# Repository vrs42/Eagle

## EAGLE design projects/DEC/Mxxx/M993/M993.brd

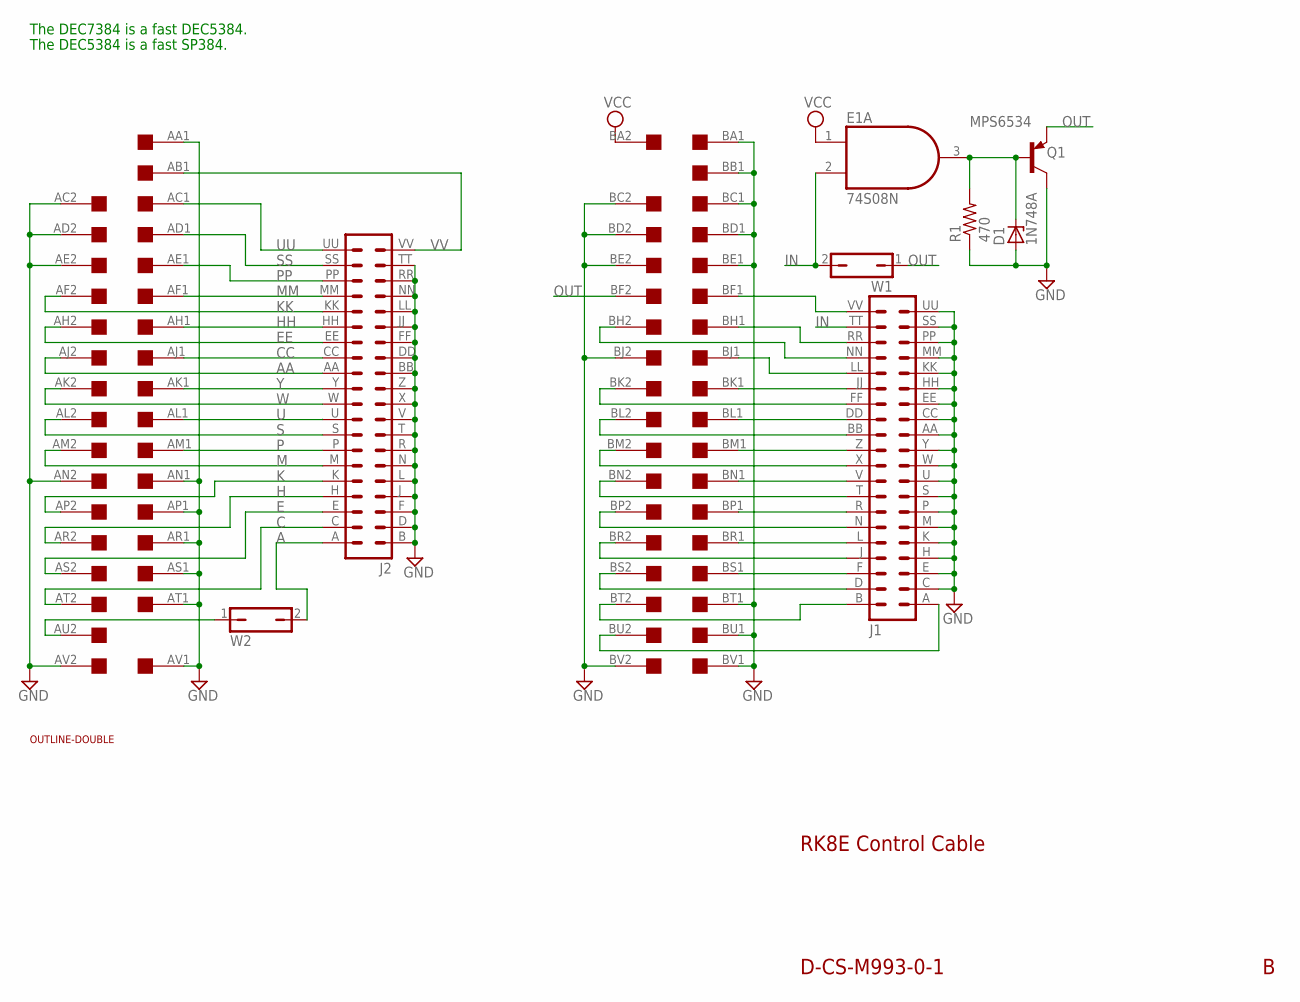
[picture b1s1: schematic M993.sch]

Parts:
D1: 1N748A; ZDIO-10
E1: 74S08N; DIL14
J1, J2: DEC40PINH
Q1: MPS6534; TO92
R1: 470; 0207/10
U$1: OUTLINE-DOUBLE; DOUBLE
U$2: DOUBLE; EDGE-CON4
W1, W2: JP1Q; JP1

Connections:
A: J2.A (1), W2.2
AA: J2.AA (23), U$2.AJ2
C: J2.C (3), U$2.AT2
CC: J2.CC (25), U$2.AJ1
E: J2.E (5), U$2.AS2
EE: J2.EE (27), U$2.AH2
GND: D1.A, E1.7 (GND), J1.AA (23), J1.C (3), J1.CC (25), J1.E (5), J1.EE (27), J1.H (7), J1.HH (29), J1.K (9), J1.KK (31), J1.M (11), J1.MM (33), J1.P (13), J1.PP (35), J1.S (15), J1.SS (37), J1.U (17), J1.UU (39), J1.W (19), J1.Y (21), J2.B (2), J2.BB (24), J2.D (4), J2.DD (26), J2.F (6), J2.FF (28), J2.J (8), J2.JJ (30), J2.L (10), J2.LL (32), J2.N (12), J2.NN (34), J2.R (14), J2.RR (36), J2.T (16), J2.TT (38), J2.V (18), J2.X (20), J2.Z (22), Q1.3 (C), R1.1, U$2.AA1, U$2.AC2, U$2.AD2, U$2.AE2, U$2.AN1, U$2.AN2, U$2.AP1, U$2.AR1, U$2.AS1, U$2.AT1, U$2.AV1, U$2.AV2, U$2.BA1, U$2.BB1, U$2.BC1, U$2.BC2, U$2.BD1, U$2.BD2, U$2.BE1, U$2.BE2, U$2.BJ2, U$2.BT1, U$2.BU1, U$2.BV1, U$2.BV2
H: J2.H (7), U$2.AR2
HH: J2.HH (29), U$2.AH1
IN: E1.2 (I1), J1.TT (38), W1.2
K: J2.K (9), U$2.AP2
KK: J2.KK (31), U$2.AF2
M: J2.M (11), U$2.AM2
MM: J2.MM (33), U$2.AF1
unnamed: U$2.AU2, W2.1
unnamed: D1.C, E1.3 (O), Q1.2 (B), R1.2
unnamed: J1.D (4), U$2.BS2
unnamed: J1.F (6), U$2.BS1
unnamed: J1.J (8), U$2.BR2
unnamed: J1.L (10), U$2.BR1
unnamed: J1.N (12), U$2.BP2
unnamed: J1.R (14), U$2.BP1
unnamed: J1.T (16), U$2.BN2
unnamed: J1.A (1), U$2.BU2
unnamed: J1.B (2), U$2.BT2
unnamed: J1.V (18), U$2.BN1
unnamed: J1.X (20), U$2.BM2
unnamed: J1.Z (22), U$2.BM1
unnamed: J1.BB (24), U$2.BL2
unnamed: J1.DD (26), U$2.BL1
unnamed: J1.FF (28), U$2.BK2
unnamed: J1.JJ (30), U$2.BK1
unnamed: J1.LL (32), U$2.BJ1
unnamed: J1.NN (34), U$2.BH2
unnamed: J1.RR (36), U$2.BH1
unnamed: J1.VV (40), U$2.BF1
OUT: Q1.1 (E), U$2.BF2, W1.1
P: J2.P (13), U$2.AM1
PP: J2.PP (35), U$2.AE1
S: J2.S (15), U$2.AL2
SS: J2.SS (37), U$2.AD1
U: J2.U (17), U$2.AL1
UU: J2.UU (39), U$2.AC1
VCC: E1.1 (I0), E1.14 (VCC), U$2.BA2
VV: J2.VV (40), U$2.AB1
W: J2.W (19), U$2.AK2
Y: J2.Y (21), U$2.AK1

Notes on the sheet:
The DEC7384 is a fast DEC5384.
The DEC5384 is a fast SP384.
RK8E Control Cable
D-CS-M993-0-1

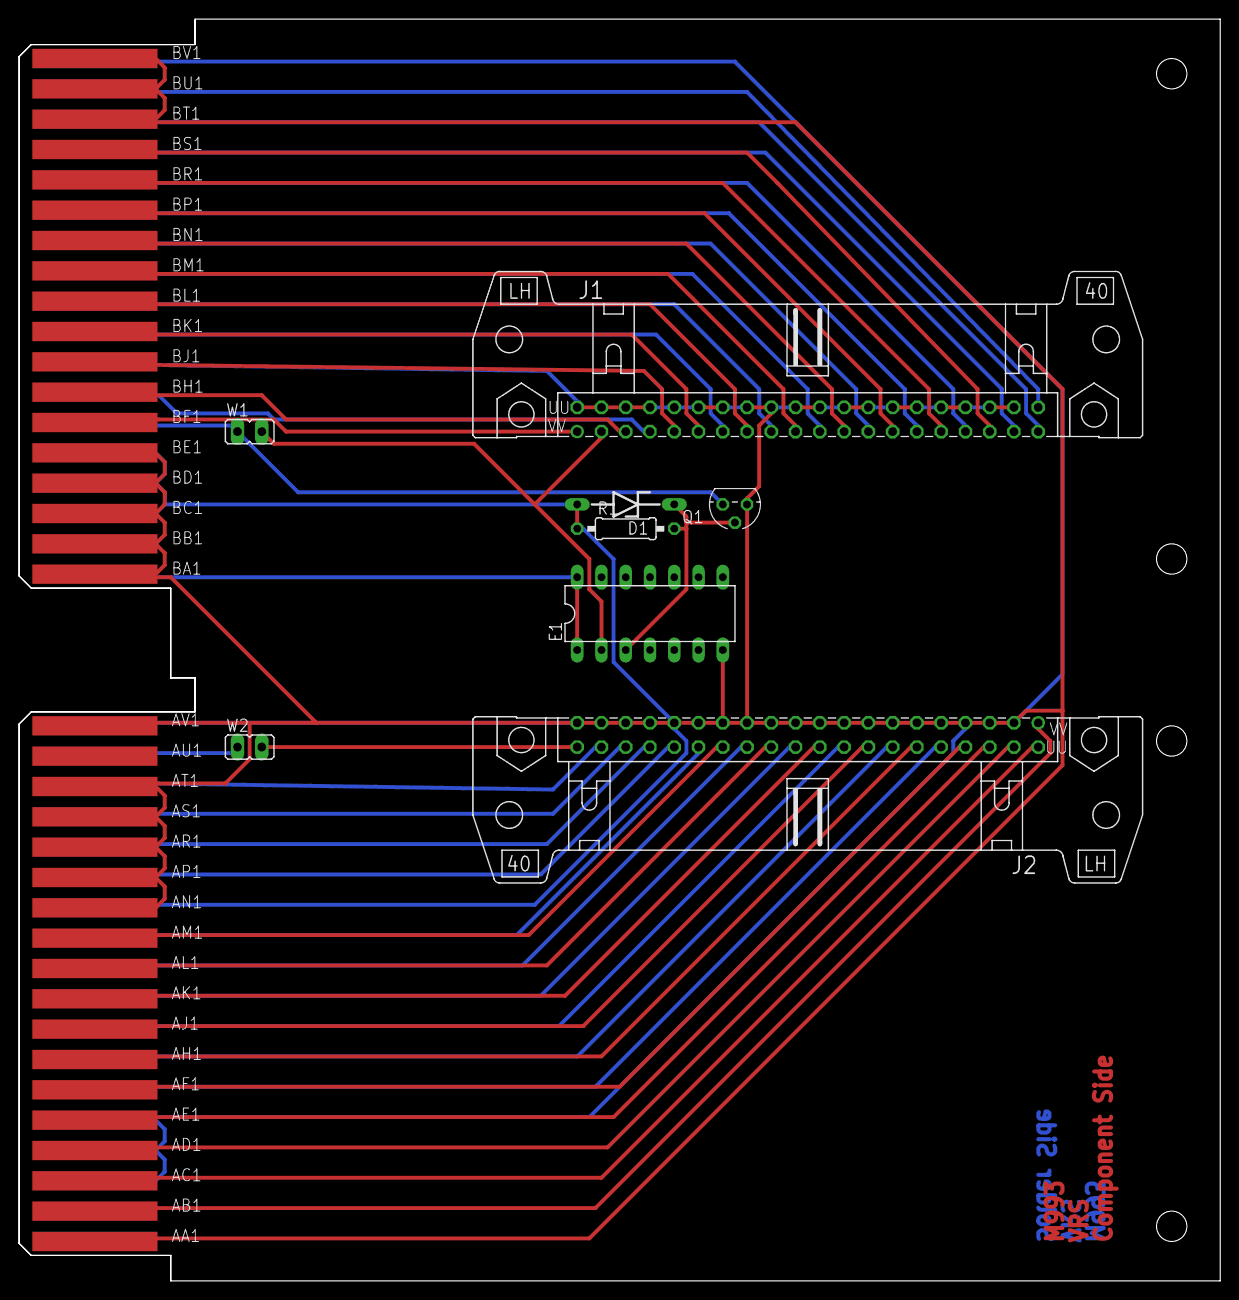
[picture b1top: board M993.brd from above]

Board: 2 copper layers, 125.7 x 132.1 mm, 10 parts (0 on the bottom side), 47 nets.

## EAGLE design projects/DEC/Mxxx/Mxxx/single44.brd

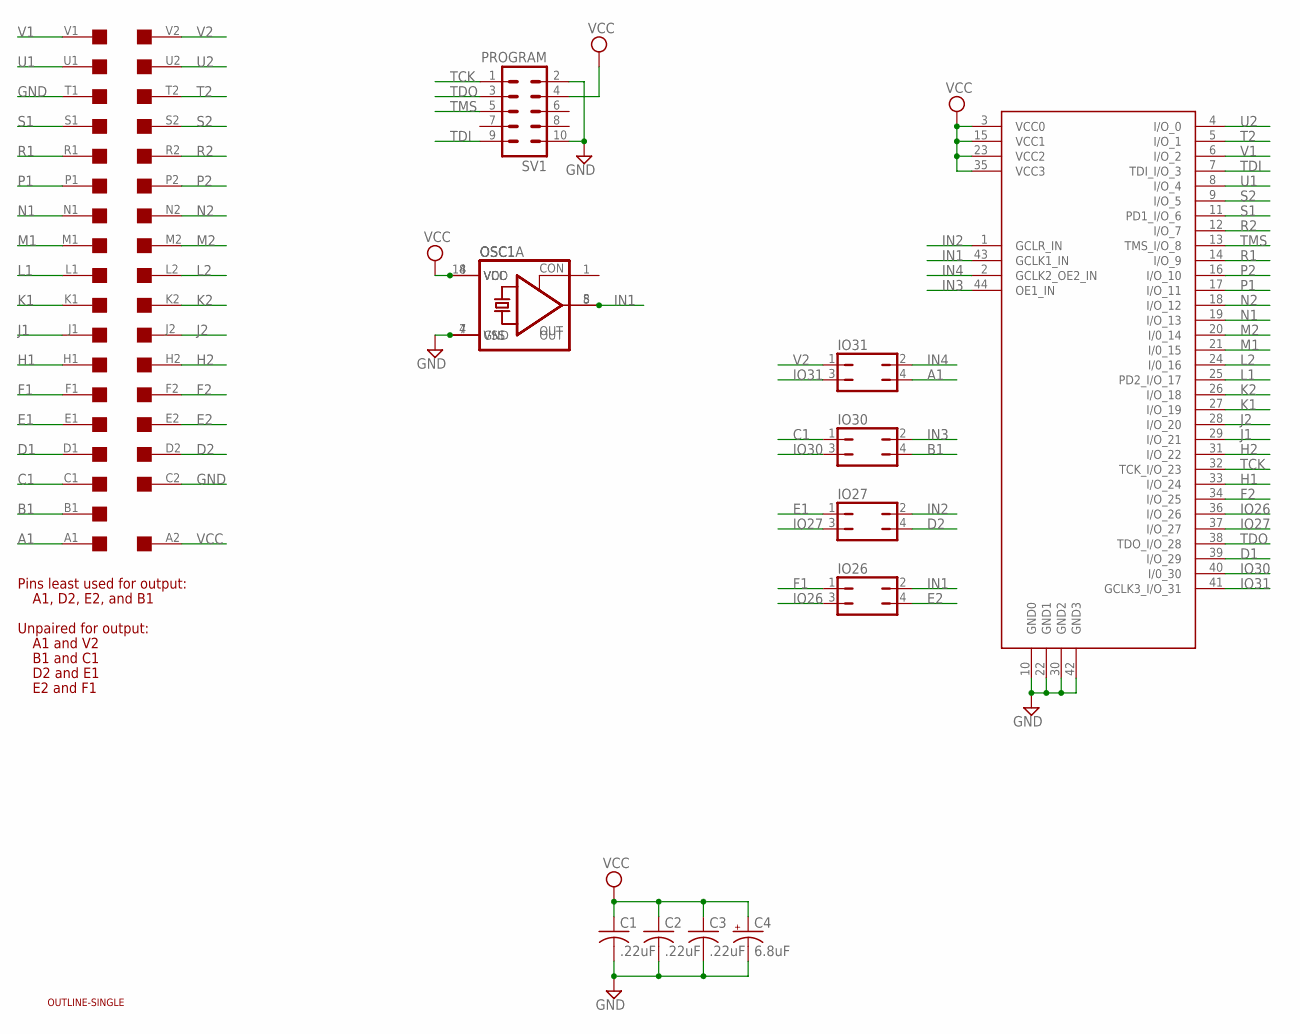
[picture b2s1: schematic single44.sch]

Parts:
C1, C2, C3: .22uF; C050-025X075
C4: 6.8uF; E15-5
IO26, IO27, IO30, IO31: JP2Q
OSC1: DIL08S
OSC1A: SG51
SV1: PROGRAM; ML10
U1: ATF1504; 3M44
U$1: OUTLINE-SINGLE; SINGLE
U$2: SINGLE; EDGE-CON2

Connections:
A1: IO31.4, U$2.A1
B1: IO30.4, U$2.B1
C1: IO30.1, U$2.C1
D1: U1.39 (I/O_29), U$2.D1
D2: IO27.4, U$2.D2
E1: IO27.1, U$2.E1
E2: IO26.4, U$2.E2
F1: IO26.1, U$2.F1
F2: U1.34 (I/O_25), U$2.F2
GND: C1.2, C2.2, C3.2, C4.-, OSC1.4 (GND), OSC1A.7 (VSS), SV1.2, SV1.10, U1.10 (GND0), U1.22 (GND1), U1.30 (GND2), U1.42 (GND3), U$2.C2, U$2.T1
H1: U1.33 (I/O_24), U$2.H1
H2: U1.31 (I/O_22), U$2.H2
IN1: IO26.2, OSC1.5 (OUT), OSC1A.8 (OUT), U1.43 (GCLK1_IN)
IN2: IO27.2, U1.1 (GCLR_IN)
IN3: IO30.2, U1.44 (OE1_IN)
IN4: IO31.2, U1.2 (GCLK2_OE2_IN)
IO26: IO26.3, U1.36 (I/O_26)
IO27: IO27.3, U1.37 (I/O_27)
IO30: IO30.3, U1.40 (I/0_30)
IO31: IO31.3, U1.41 (GCLK3_I/O_31)
J1: U1.29 (I/O_21), U$2.J1
J2: U1.28 (I/O_20), U$2.J2
K1: U1.27 (I/O_19), U$2.K1
K2: U1.26 (I/O_18), U$2.K2
L1: U1.25 (PD2_I/O_17), U$2.L1
L2: U1.24 (I/0_16), U$2.L2
M1: U1.21 (I/0_15), U$2.M1
M2: U1.20 (I/0_14), U$2.M2
N1: U1.19 (I/O_13), U$2.N1
N2: U1.18 (I/O_12), U$2.N2
P1: U1.17 (I/O_11), U$2.P1
P2: U1.16 (I/O_10), U$2.P2
R1: U1.14 (I/O_9), U$2.R1
R2: U1.12 (I/O_7), U$2.R2
S1: U1.11 (PD1_I/O_6), U$2.S1
S2: U1.9 (I/O_5), U$2.S2
T2: U1.5 (I/O_1), U$2.T2
TCK: SV1.1, U1.32 (TCK_I/O_23)
TDI: SV1.9, U1.7 (TDI_I/O_3)
TDO: SV1.3, U1.38 (TDO_I/O_28)
TMS: SV1.5, U1.13 (TMS_I/O_8)
U1: U1.8 (I/O_4), U$2.U1
U2: U1.4 (I/O_0), U$2.U2
V1: U1.6 (I/O_2), U$2.V1
V2: IO31.1, U$2.V2
VCC: C1.1, C2.1, C3.1, C4.+, OSC1.8 (VCC), OSC1A.14 (VDD), SV1.4, U1.3 (VCC0), U1.15 (VCC1), U1.23 (VCC2), U1.35 (VCC3), U$2.A2

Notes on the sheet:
Pins least used for output:
A1, D2, E2, and B1
Unpaired for output:
A1 and V2
B1 and C1
D2 and E1
E2 and F1

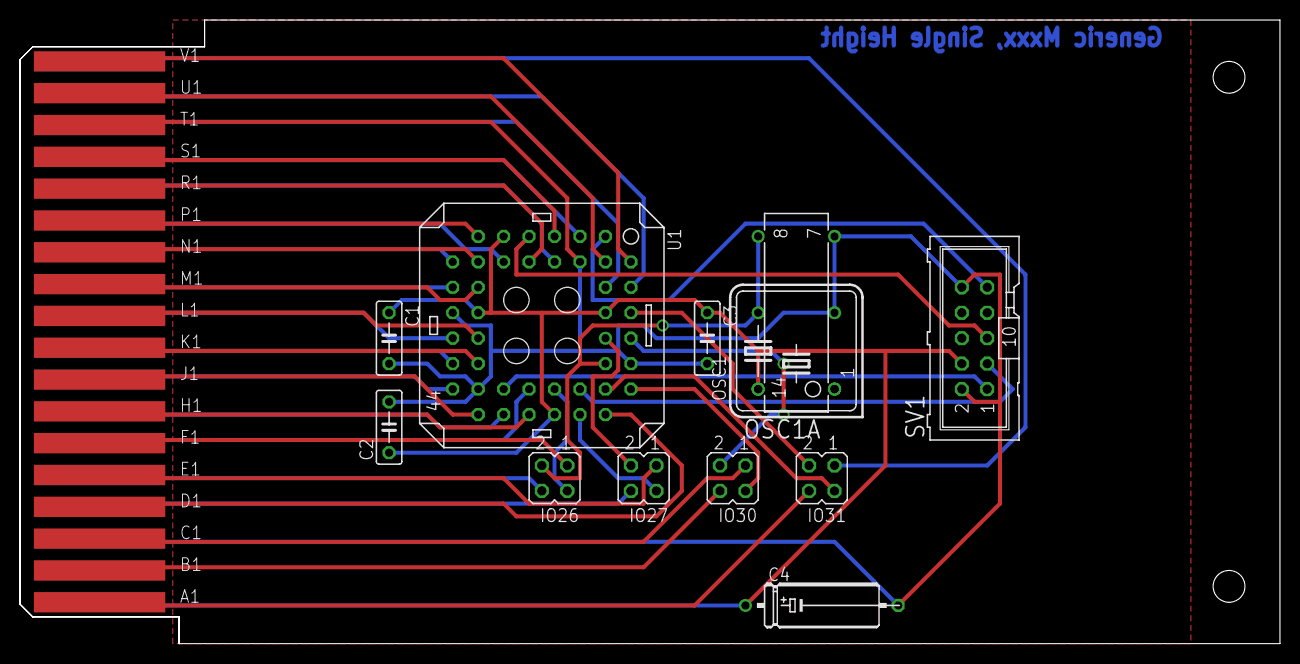
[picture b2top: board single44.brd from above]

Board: 2 copper layers, 125.7 x 62.2 mm, 14 parts (0 on the bottom side), 46 nets.

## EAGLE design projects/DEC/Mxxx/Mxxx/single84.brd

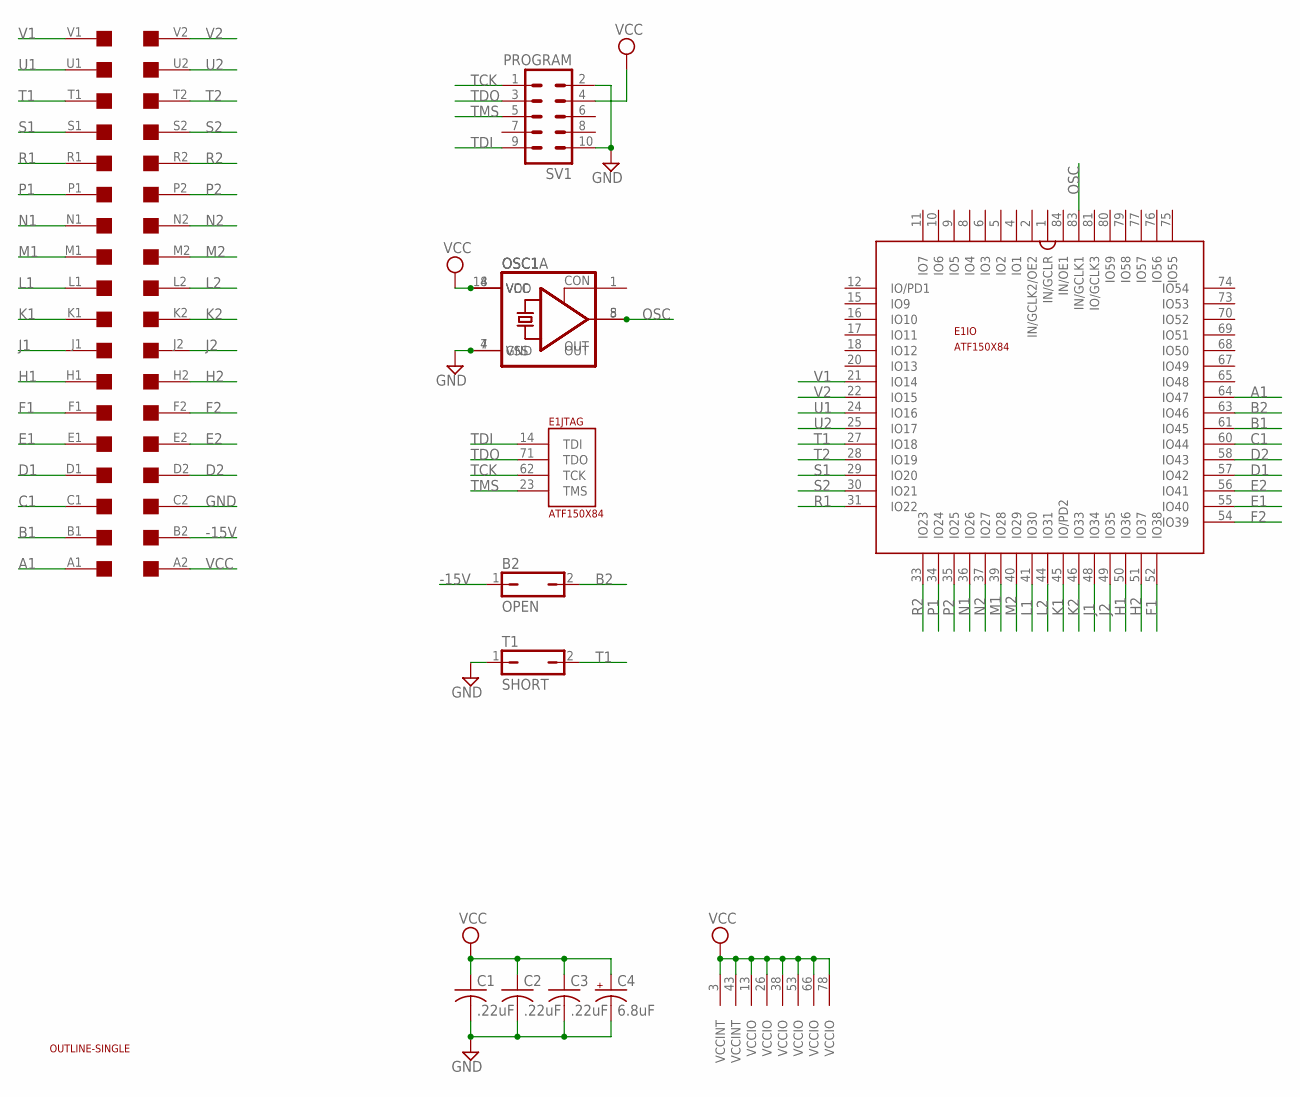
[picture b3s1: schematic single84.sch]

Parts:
B2: OPEN; JP1
C1, C2, C3: .22uF; C050-025X075
C4: 6.8uF; E15-5
E1: ATF150X84; S84
OSC1: DIL08S
OSC1A: SG51
SV1: PROGRAM; ML10
T1: SHORT; JP1
U$1: OUTLINE-SINGLE; SINGLE
U$2: SINGLE; EDGE-CON2

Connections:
-15V: B2.1, U$2.B2
A1: E1.64 (IO47), U$2.A1
B1: E1.61 (IO45), U$2.B1
B2: B2.2, E1.63 (IO46)
C1: E1.60 (IO44), U$2.C1
D1: E1.57 (IO42), U$2.D1
D2: E1.58 (IO43), U$2.D2
E1: E1.55 (IO40), U$2.E1
E2: E1.56 (IO41), U$2.E2
F1: E1.52 (IO38), U$2.F1
F2: E1.54 (IO39), U$2.F2
GND: C1.2, C2.2, C3.2, C4.-, E1.7 (GND), E1.19 (GND), E1.32 (GND), E1.42 (GND), E1.47 (GND), E1.59 (GND), E1.72 (GND), E1.82 (GND), OSC1.4 (GND), OSC1A.7 (VSS), SV1.2, SV1.10, T1.1, U$2.C2
H1: E1.50 (IO36), U$2.H1
H2: E1.51 (IO37), U$2.H2
J1: E1.48 (IO34), U$2.J1
J2: E1.49 (IO35), U$2.J2
K1: E1.45 (IO/PD2), U$2.K1
K2: E1.46 (IO33), U$2.K2
L1: E1.41 (IO30), U$2.L1
L2: E1.44 (IO31), U$2.L2
M1: E1.39 (IO28), U$2.M1
M2: E1.40 (IO29), U$2.M2
N1: E1.36 (IO26), U$2.N1
N2: E1.37 (IO27), U$2.N2
OSC: E1.83 (IN/GCLK1), OSC1.5 (OUT), OSC1A.8 (OUT)
P1: E1.34 (IO24), U$2.P1
P2: E1.35 (IO25), U$2.P2
R1: E1.31 (IO22), U$2.R1
R2: E1.33 (IO23), U$2.R2
S1: E1.29 (IO20), U$2.S1
S2: E1.30 (IO21), U$2.S2
T1: E1.27 (IO18), T1.2, U$2.T1
T2: E1.28 (IO19), U$2.T2
TCK: E1.62 (TCK), SV1.1
TDI: E1.14 (TDI), SV1.9
TDO: E1.71 (TDO), SV1.3
TMS: E1.23 (TMS), SV1.5
U1: E1.24 (IO16), U$2.U1
U2: E1.25 (IO17), U$2.U2
V1: E1.21 (IO14), U$2.V1
V2: E1.22 (IO15), U$2.V2
VCC: C1.1, C2.1, C3.1, C4.+, E1.3 (VCCINT), E1.13 (VCCIO), E1.26 (VCCIO), E1.38 (VCCIO), E1.43 (VCCINT), E1.53 (VCCIO), E1.66 (VCCIO), E1.78 (VCCIO), OSC1.8 (VCC), OSC1A.14 (VDD), SV1.4, U$2.A2

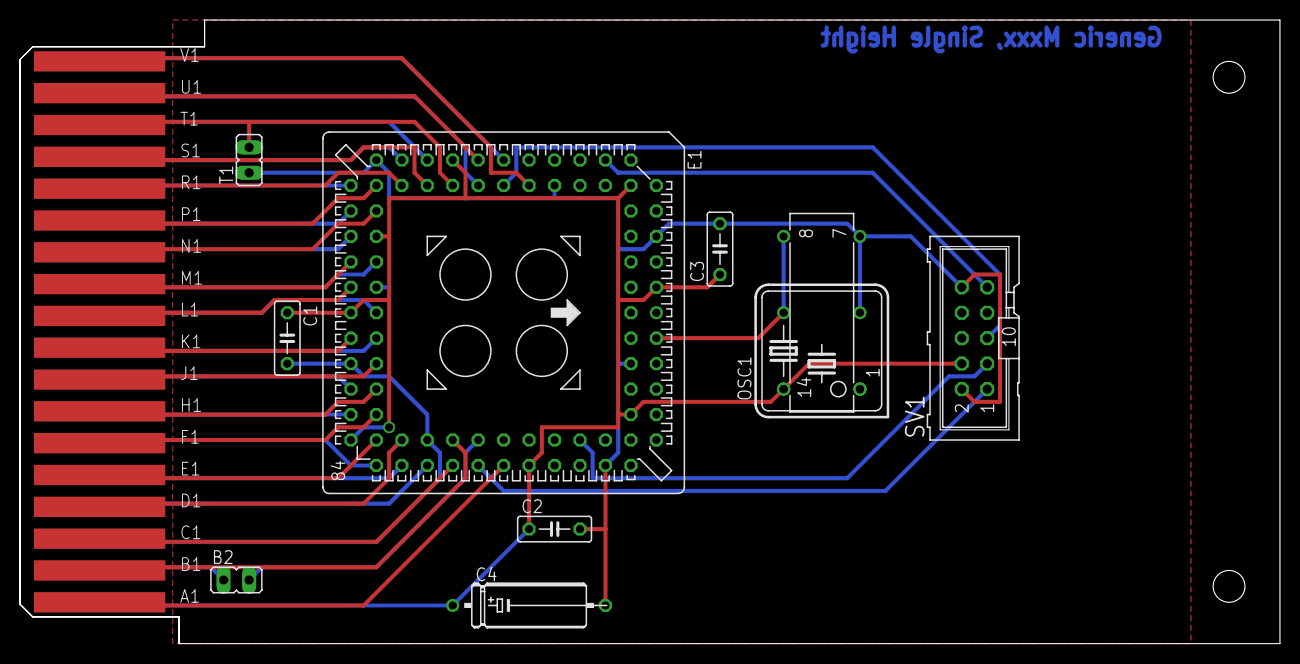
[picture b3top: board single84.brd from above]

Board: 2 copper layers, 125.7 x 62.2 mm, 12 parts (0 on the bottom side), 42 nets.

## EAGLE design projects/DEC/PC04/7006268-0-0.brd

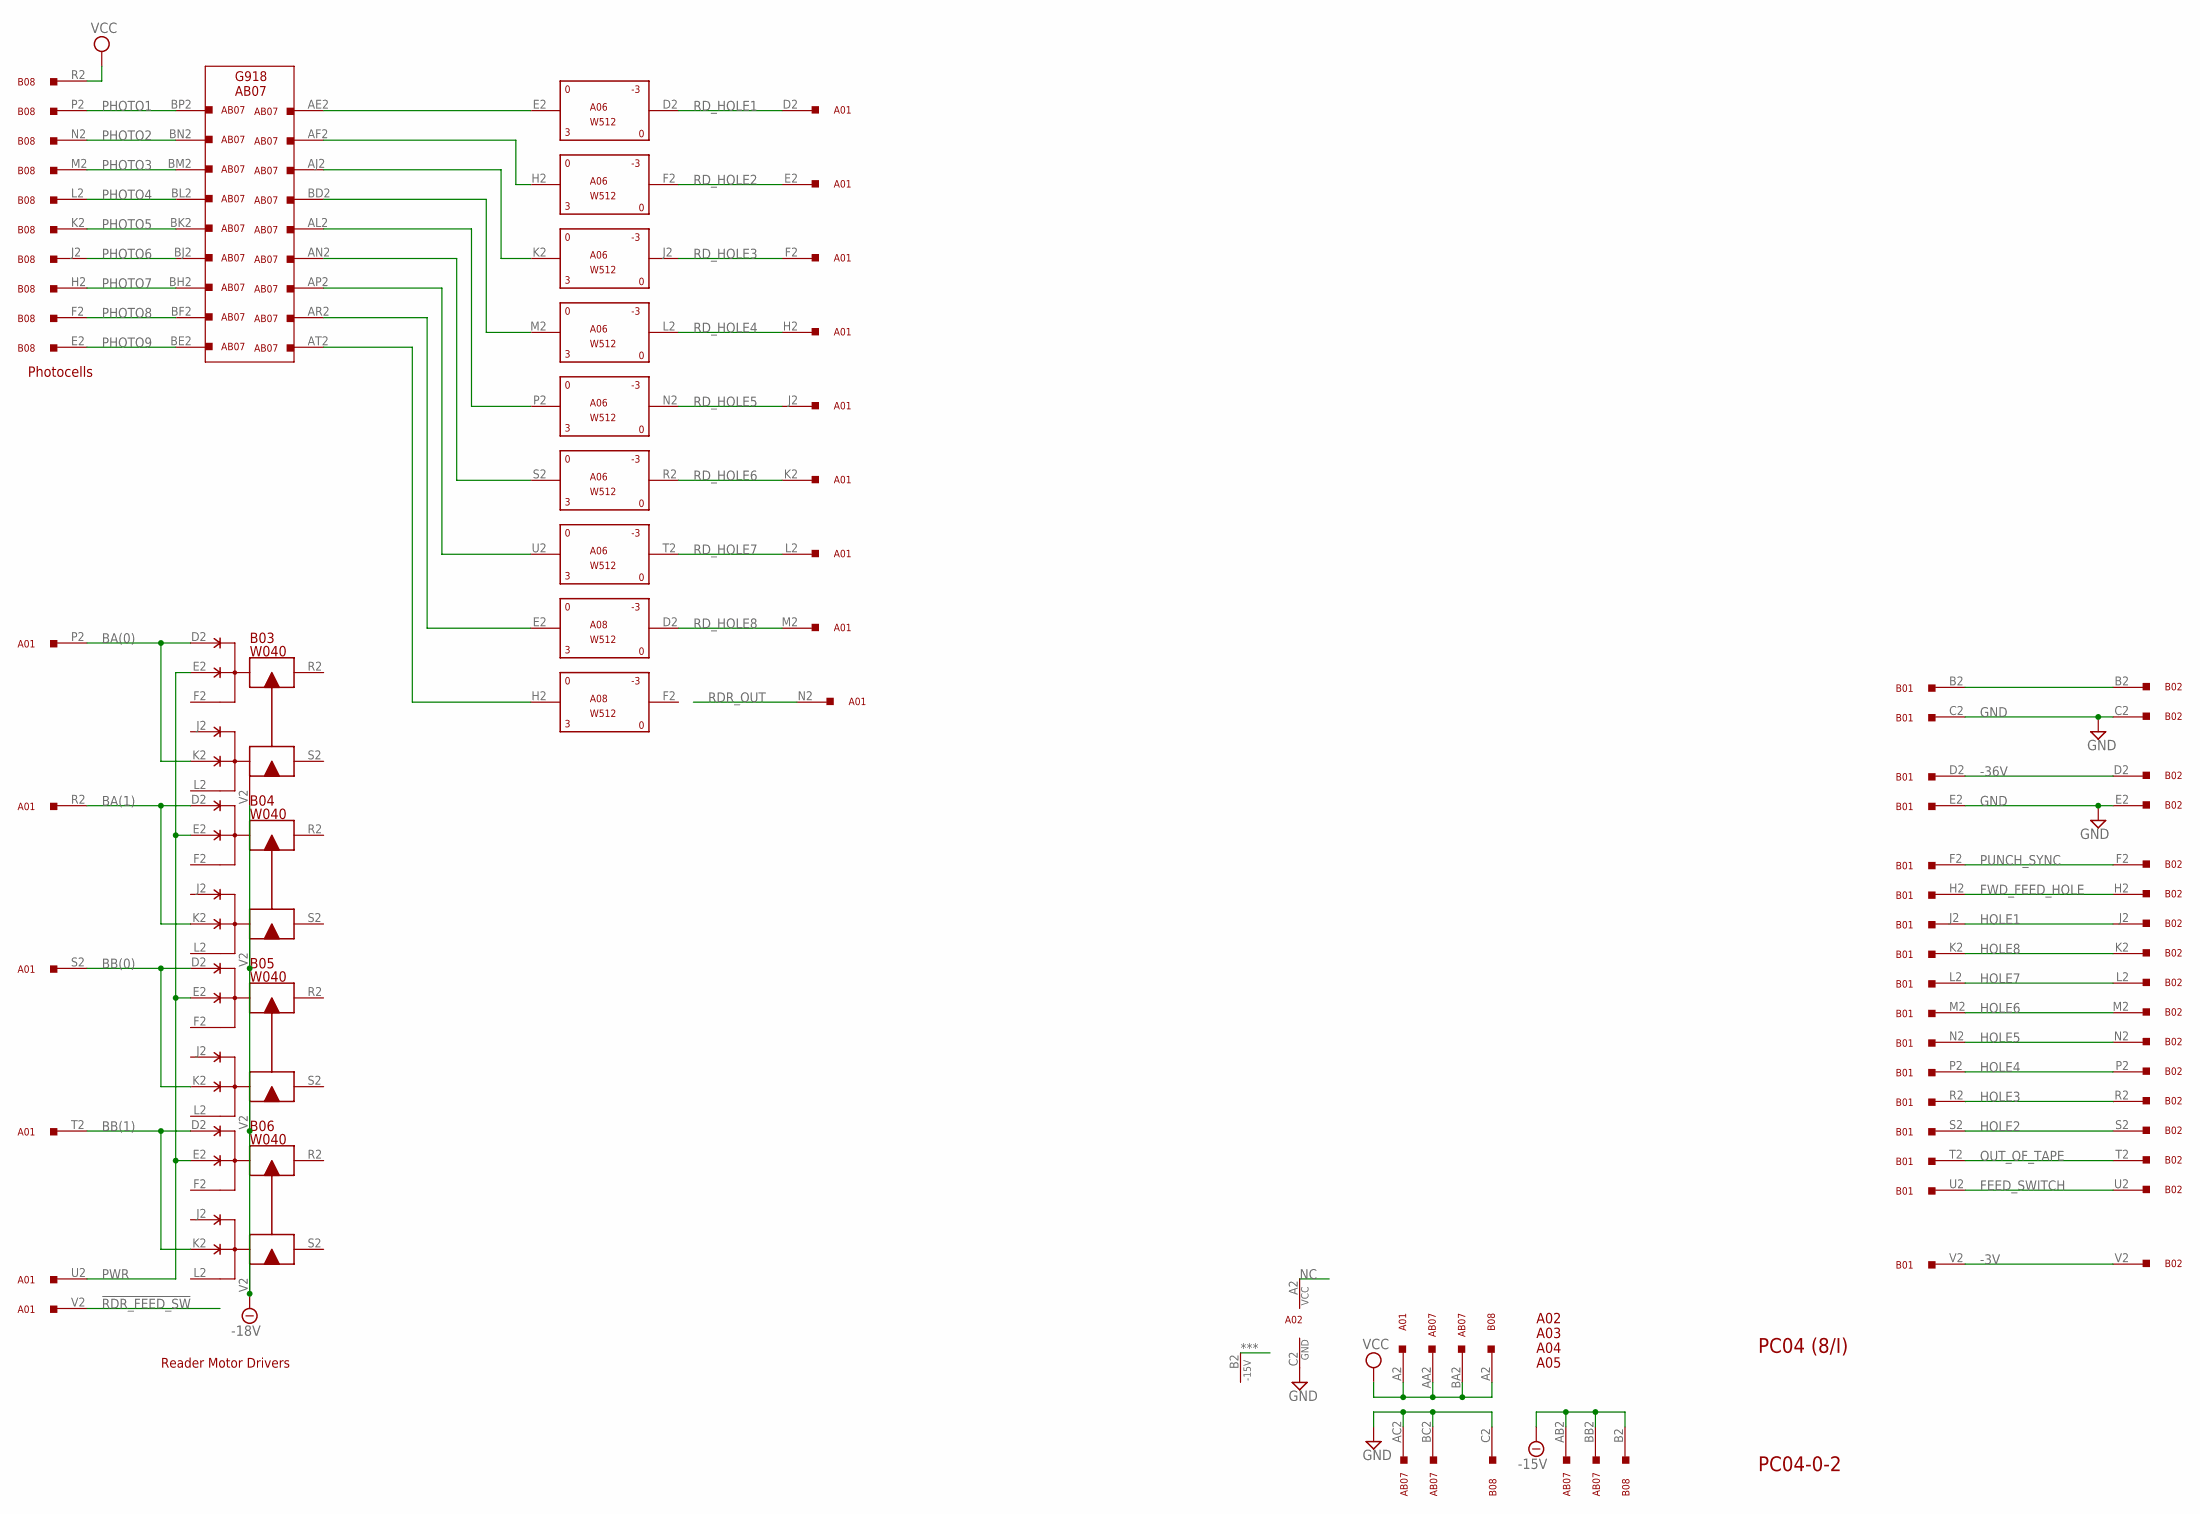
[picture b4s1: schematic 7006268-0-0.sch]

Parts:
A01: W033; H807
A02, A03, A04, A05: EMPTY; H807
A06, A08: W512; H807
AB07: G918; H807-2
B01, B02, B08: W033; H807
B03, B04, B05, B06: W040; H807

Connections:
!RDR_FEED_SW: A01.V2
***: A02.B2 (-15V)
-3V: B01.V2, B02.V2
-15V: A03.B2 (-15V), A04.B2 (-15V), A05.B2 (-15V), A06.B2 (-15V), A08.B2 (-15V), AB07.AB2, AB07.BB2, B03.B2 (-15V), B04.B2 (-15V), B05.B2 (-15V), B06.B2 (-15V), B08.B2
-18V: B03.V2 (V), B04.V2 (V), B05.V2 (V), B06.V2 (V)
-36V: B01.D2, B02.D2
BA(0): A01.P2, B03.D2 (D), B03.K2 (K)
BA(1): A01.R2, B04.D2 (D), B04.K2 (K)
BB(0): A01.S2, B05.D2 (D), B05.K2 (K)
BB(1): A01.T2, B06.D2 (D), B06.K2 (K)
FEED_SWITCH: B01.U2, B02.U2
FWD_FEED_HOLE: B01.H2, B02.H2
GND: A02.C2 (GND), A03.C2 (GND), A04.C2 (GND), A05.C2 (GND), A06.C2 (GND), A08.C2 (GND), AB07.AC2, AB07.BC2, B01.C2, B01.E2, B02.C2, B02.E2, B03.C2 (GND), B04.C2 (GND), B05.C2 (GND), B06.C2 (GND), B08.C2
HOLE1: B01.J2, B02.J2
HOLE2: B01.S2, B02.S2
HOLE3: B01.R2, B02.R2
HOLE4: B01.P2, B02.P2
HOLE5: B01.N2, B02.N2
HOLE6: B01.M2, B02.M2
HOLE7: B01.L2, B02.L2
HOLE8: B01.K2, B02.K2
unnamed: A06.E2 (IN), AB07.AE2
unnamed: A06.H2 (IN), AB07.AF2
unnamed: B01.B2, B02.B2
unnamed: A06.K2 (IN), AB07.AJ2
unnamed: A06.M2 (IN), AB07.BD2
unnamed: A06.P2 (IN), AB07.AL2
unnamed: A06.S2 (IN), AB07.AN2
unnamed: A06.U2 (IN), AB07.AP2
unnamed: A08.E2 (IN), AB07.AR2
unnamed: A08.H2 (IN), AB07.AT2
NC: A02.A2 (VCC)
OUT_OF_TAPE: B01.T2, B02.T2
PHOTO1: AB07.BP2, B08.P2
PHOTO2: AB07.BN2, B08.N2
PHOTO3: AB07.BM2, B08.M2
PHOTO4: AB07.BL2, B08.L2
PHOTO5: AB07.BK2, B08.K2
PHOTO6: AB07.BJ2, B08.J2
PHOTO7: AB07.BH2, B08.H2
PHOTO8: AB07.BF2, B08.F2
PHOTO9: AB07.BE2, B08.E2
PUNCH_SYNC: B01.F2, B02.F2
PWR: A01.U2, B03.E2 (E), B04.E2 (E), B05.E2 (E), B06.E2 (E)
RDR_OUT: A01.N2
RD_HOLE1: A01.D2, A06.D2 (OUT)
RD_HOLE2: A01.E2, A06.F2 (OUT)
RD_HOLE3: A01.F2, A06.J2 (OUT)
RD_HOLE4: A01.H2, A06.L2 (OUT)
RD_HOLE5: A01.J2, A06.N2 (OUT)
RD_HOLE6: A01.K2, A06.R2 (OUT)
RD_HOLE7: A01.L2, A06.T2 (OUT)
RD_HOLE8: A01.M2, A08.D2 (OUT)
VCC: A01.A2, A03.A2 (VCC), A04.A2 (VCC), A05.A2 (VCC), A06.A2 (VCC), A08.A2 (VCC), AB07.AA2, AB07.BA2, B03.A2 (VCC), B04.A2 (VCC), B05.A2 (VCC), B06.A2 (VCC), B08.A2, B08.R2

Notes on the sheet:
PC04 (8/I)
PC04-0-2
Photocells
G918
AB07
Reader Motor Drivers

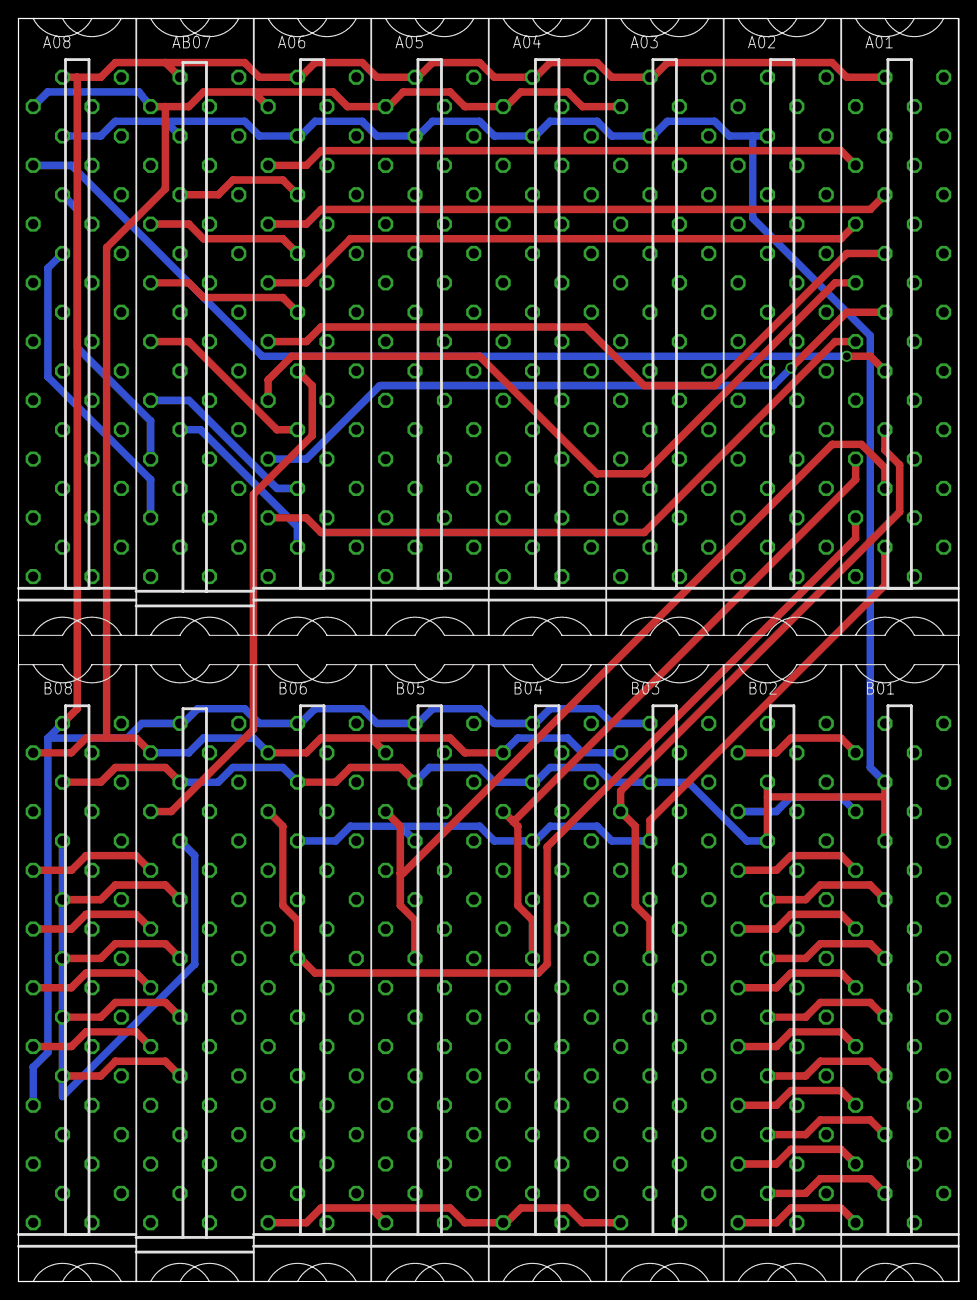
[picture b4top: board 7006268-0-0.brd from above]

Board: 2 copper layers, 101.6 x 136.5 mm, 15 parts (0 on the bottom side), 50 nets.

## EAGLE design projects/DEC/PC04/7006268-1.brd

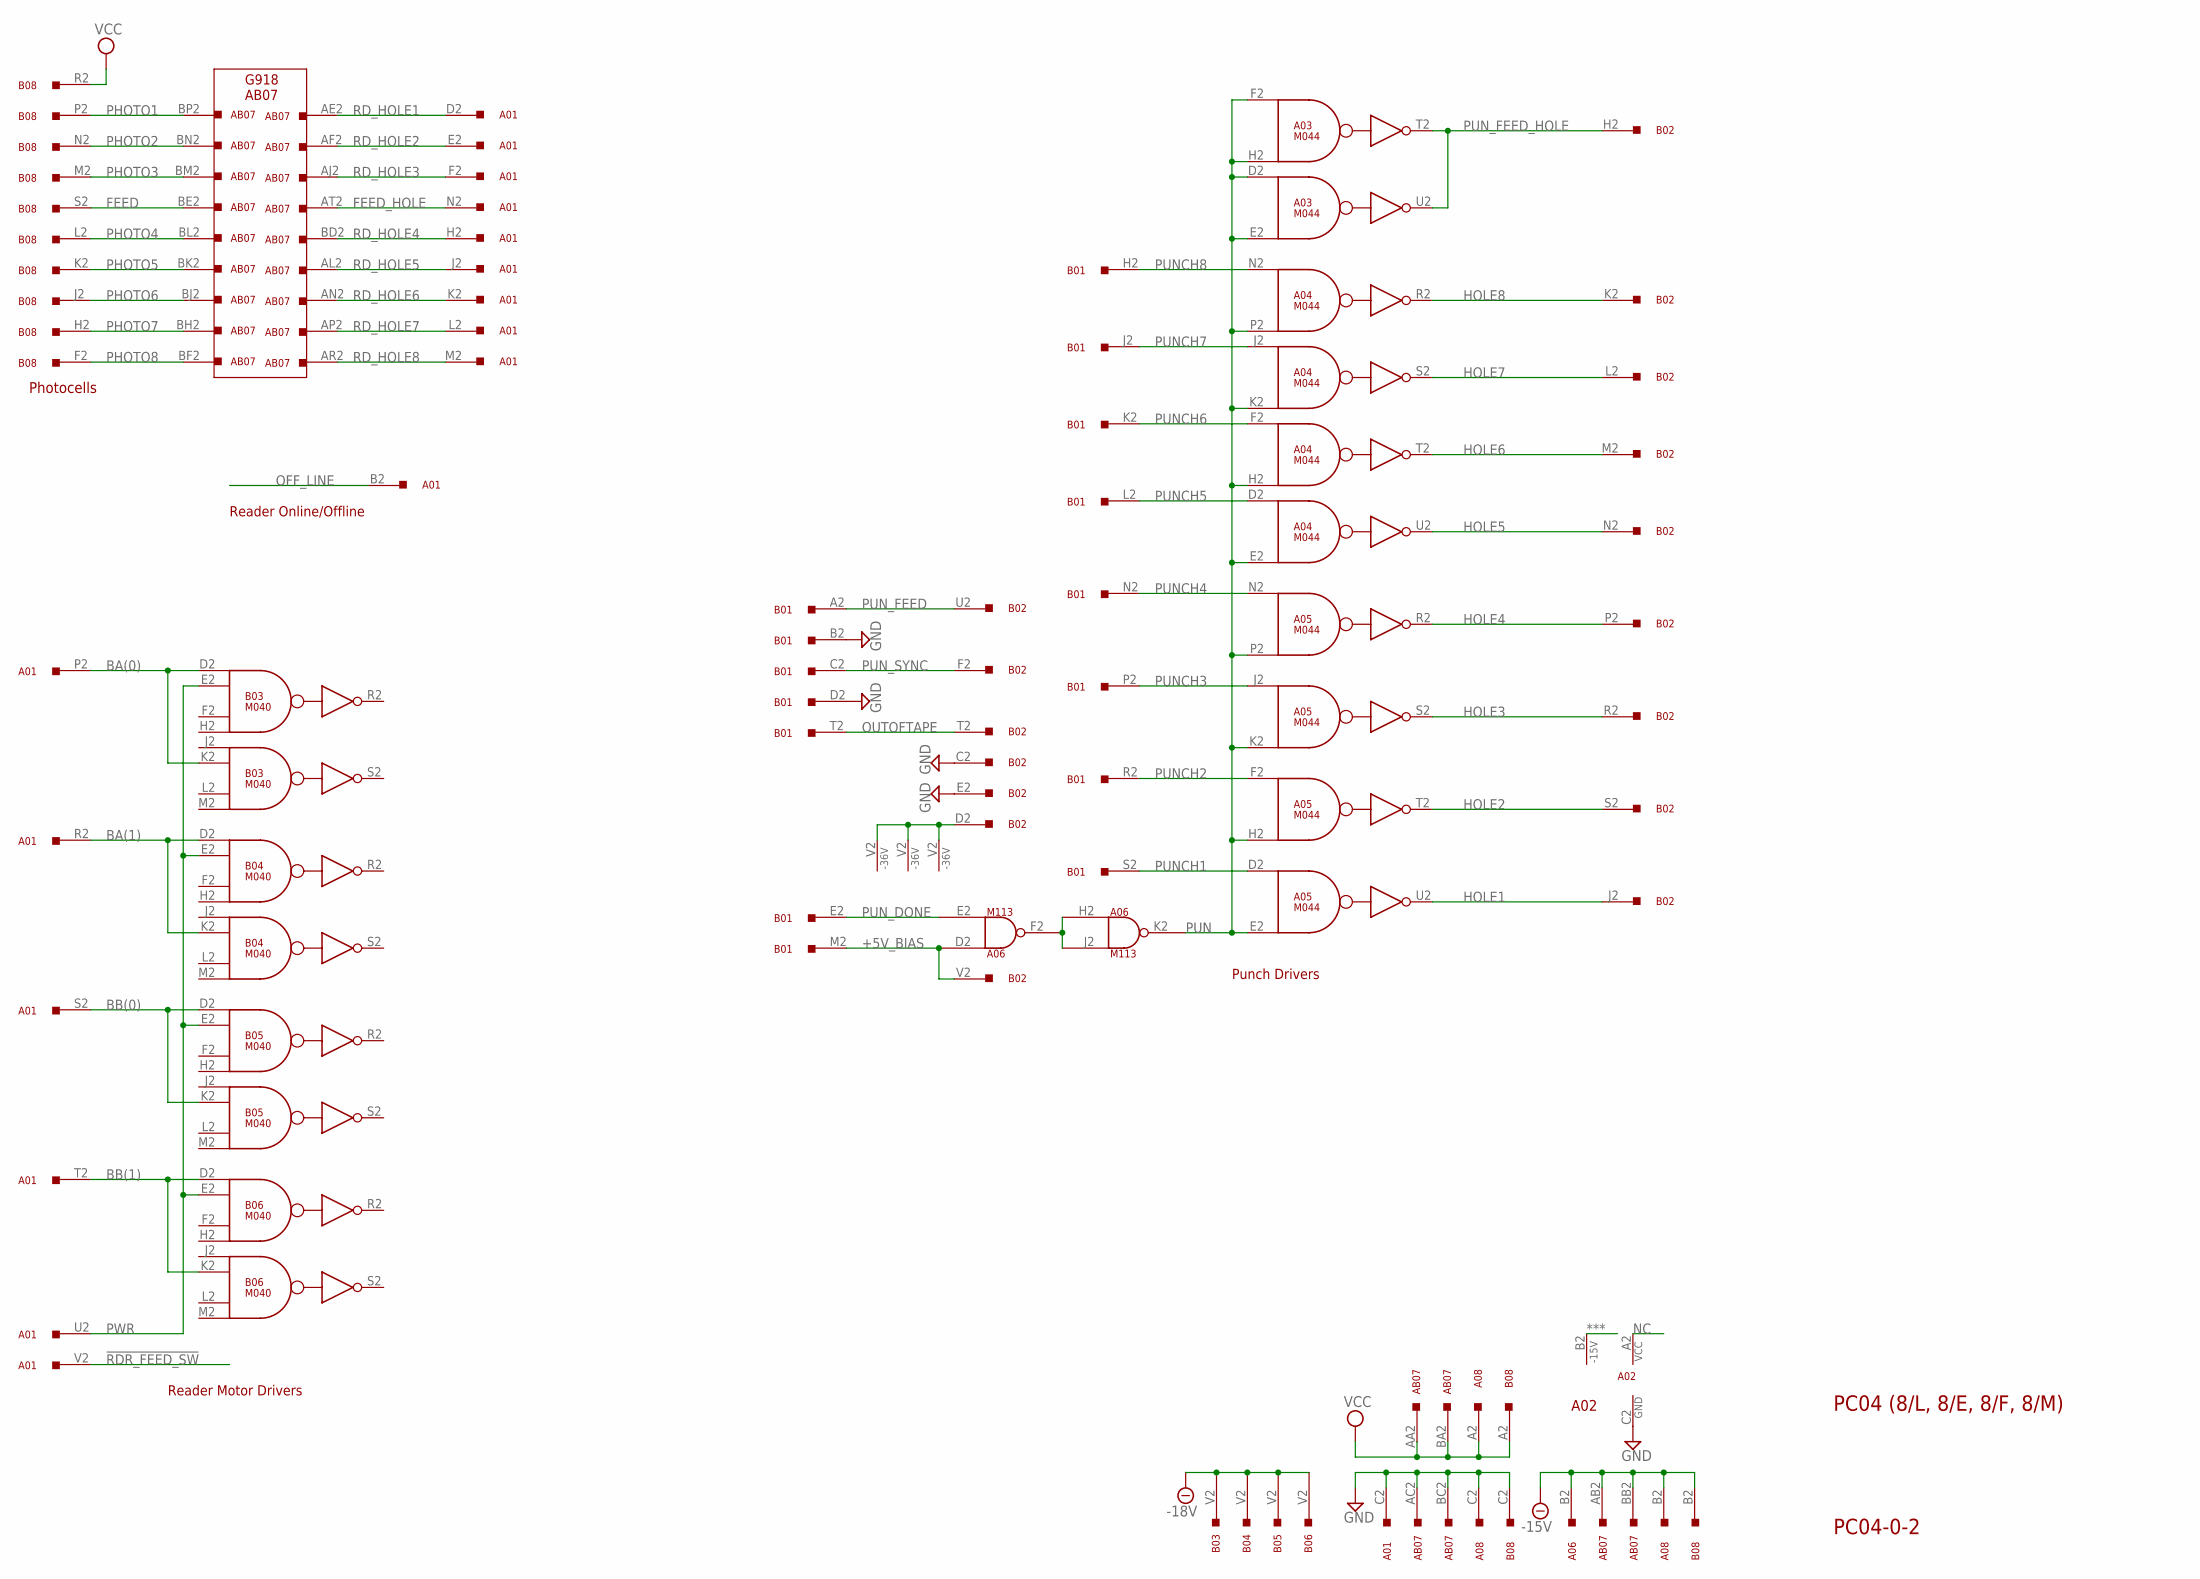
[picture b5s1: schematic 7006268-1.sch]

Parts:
A01, A08: W033; H807
A02: EMPTY; H807
A03, A04, A05: M044; H807
A06: M113; H807
AB07: G918; H807-2
B01, B02, B08: W033; H807
B03, B04, B05, B06: M040; H807

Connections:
!RDR_FEED_SW: A01.V2
***: A02.B2 (-15V)
+5V_BIAS: A06.D2 (IN1), B01.M2, B02.V2
-15V: A03.B2 (-15V), A04.B2 (-15V), A05.B2 (-15V), A06.B2, A08.B2, AB07.AB2, AB07.BB2, B03.B2 (-15V), B04.B2 (-15V), B05.B2 (-15V), B06.B2 (-15V), B08.B2
-18V: B03.V2, B04.V2, B05.V2, B06.V2
-36V: A03.V2 (-36V), A04.V2 (-36V), A05.V2 (-36V), B02.D2
BA(0): A01.P2, B03.D2 (D), B03.K2 (E)
BA(1): A01.R2, B04.D2 (D), B04.K2 (E)
BB(0): A01.S2, B05.D2 (D), B05.K2 (E)
BB(1): A01.T2, B06.D2 (D), B06.K2 (E)
FEED: AB07.BE2, B08.S2
FEED_HOLE: A01.N2, AB07.AT2
GND: A01.C2, A02.C2 (GND), A03.C2 (GND), A03.M2 (GND), A04.C2 (GND), A04.M2 (GND), A05.C2 (GND), A05.M2 (GND), A06.C2 (GND), A06.T1 (GND), A08.C2, AB07.AC2, AB07.BC2, B01.B2, B01.D2, B02.C2, B02.E2, B03.C2 (GND), B04.C2 (GND), B05.C2 (GND), B06.C2 (GND), B08.C2
HOLE1: A05.U2 (R), B02.J2
HOLE2: A05.T2 (R), B02.S2
HOLE3: A05.S2 (R), B02.R2
HOLE4: A05.R2 (R), B02.P2
HOLE5: A04.U2 (R), B02.N2
HOLE6: A04.T2 (R), B02.M2
HOLE7: A04.S2 (R), B02.L2
HOLE8: A04.R2 (R), B02.K2
unnamed: A06.F2 (OUT), A06.H2 (IN1), A06.J2 (IN2)
NC: A02.A2 (VCC)
OFF_LINE: A01.B2
OUTOFTAPE: B01.T2, B02.T2
PHOTO1: AB07.BP2, B08.P2
PHOTO2: AB07.BN2, B08.N2
PHOTO3: AB07.BM2, B08.M2
PHOTO4: AB07.BL2, B08.L2
PHOTO5: AB07.BK2, B08.K2
PHOTO6: AB07.BJ2, B08.J2
PHOTO7: AB07.BH2, B08.H2
PHOTO8: AB07.BF2, B08.F2
PUN: A03.D2 (D), A03.E2 (H), A03.F2 (D), A03.H2 (H), A04.E2 (H), A04.H2 (H), A04.K2 (H), A04.P2 (H), A05.E2 (H), A05.H2 (H), A05.K2 (H), A05.P2 (H), A06.K2 (OUT)
PUNCH1: A05.D2 (D), B01.S2
PUNCH2: A05.F2 (D), B01.R2
PUNCH3: A05.J2 (D), B01.P2
PUNCH4: A05.N2 (D), B01.N2
PUNCH5: A04.D2 (D), B01.L2
PUNCH6: A04.F2 (D), B01.K2
PUNCH7: A04.J2 (D), B01.J2
PUNCH8: A04.N2 (D), B01.H2
PUN_DONE: A06.E2 (IN2), B01.E2
PUN_FEED: B01.A2, B02.U2
PUN_FEED_HOLE: A03.T2 (R), A03.U2 (R), B02.H2
PUN_SYNC: B01.C2, B02.F2
PWR: A01.U2, B03.E2 (E), B04.E2 (E), B05.E2 (E), B06.E2 (E)
RD_HOLE1: A01.D2, AB07.AE2
RD_HOLE2: A01.E2, AB07.AF2
RD_HOLE3: A01.F2, AB07.AJ2
RD_HOLE4: A01.H2, AB07.BD2
RD_HOLE5: A01.J2, AB07.AL2
RD_HOLE6: A01.K2, AB07.AN2
RD_HOLE7: A01.L2, AB07.AP2
RD_HOLE8: A01.M2, AB07.AR2
VCC: A03.A2 (VCC), A04.A2 (VCC), A05.A2 (VCC), A06.A2 (VCC), A08.A2, AB07.AA2, AB07.BA2, B03.A2 (VCC), B04.A2 (VCC), B05.A2 (VCC), B06.A2 (VCC), B08.A2, B08.R2

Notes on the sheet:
PC04 (8/L, 8/E, 8/F, 8/M)
PC04-0-2
Photocells
G918
AB07
Reader Online/Offline
Reader Motor Drivers
Punch Drivers
